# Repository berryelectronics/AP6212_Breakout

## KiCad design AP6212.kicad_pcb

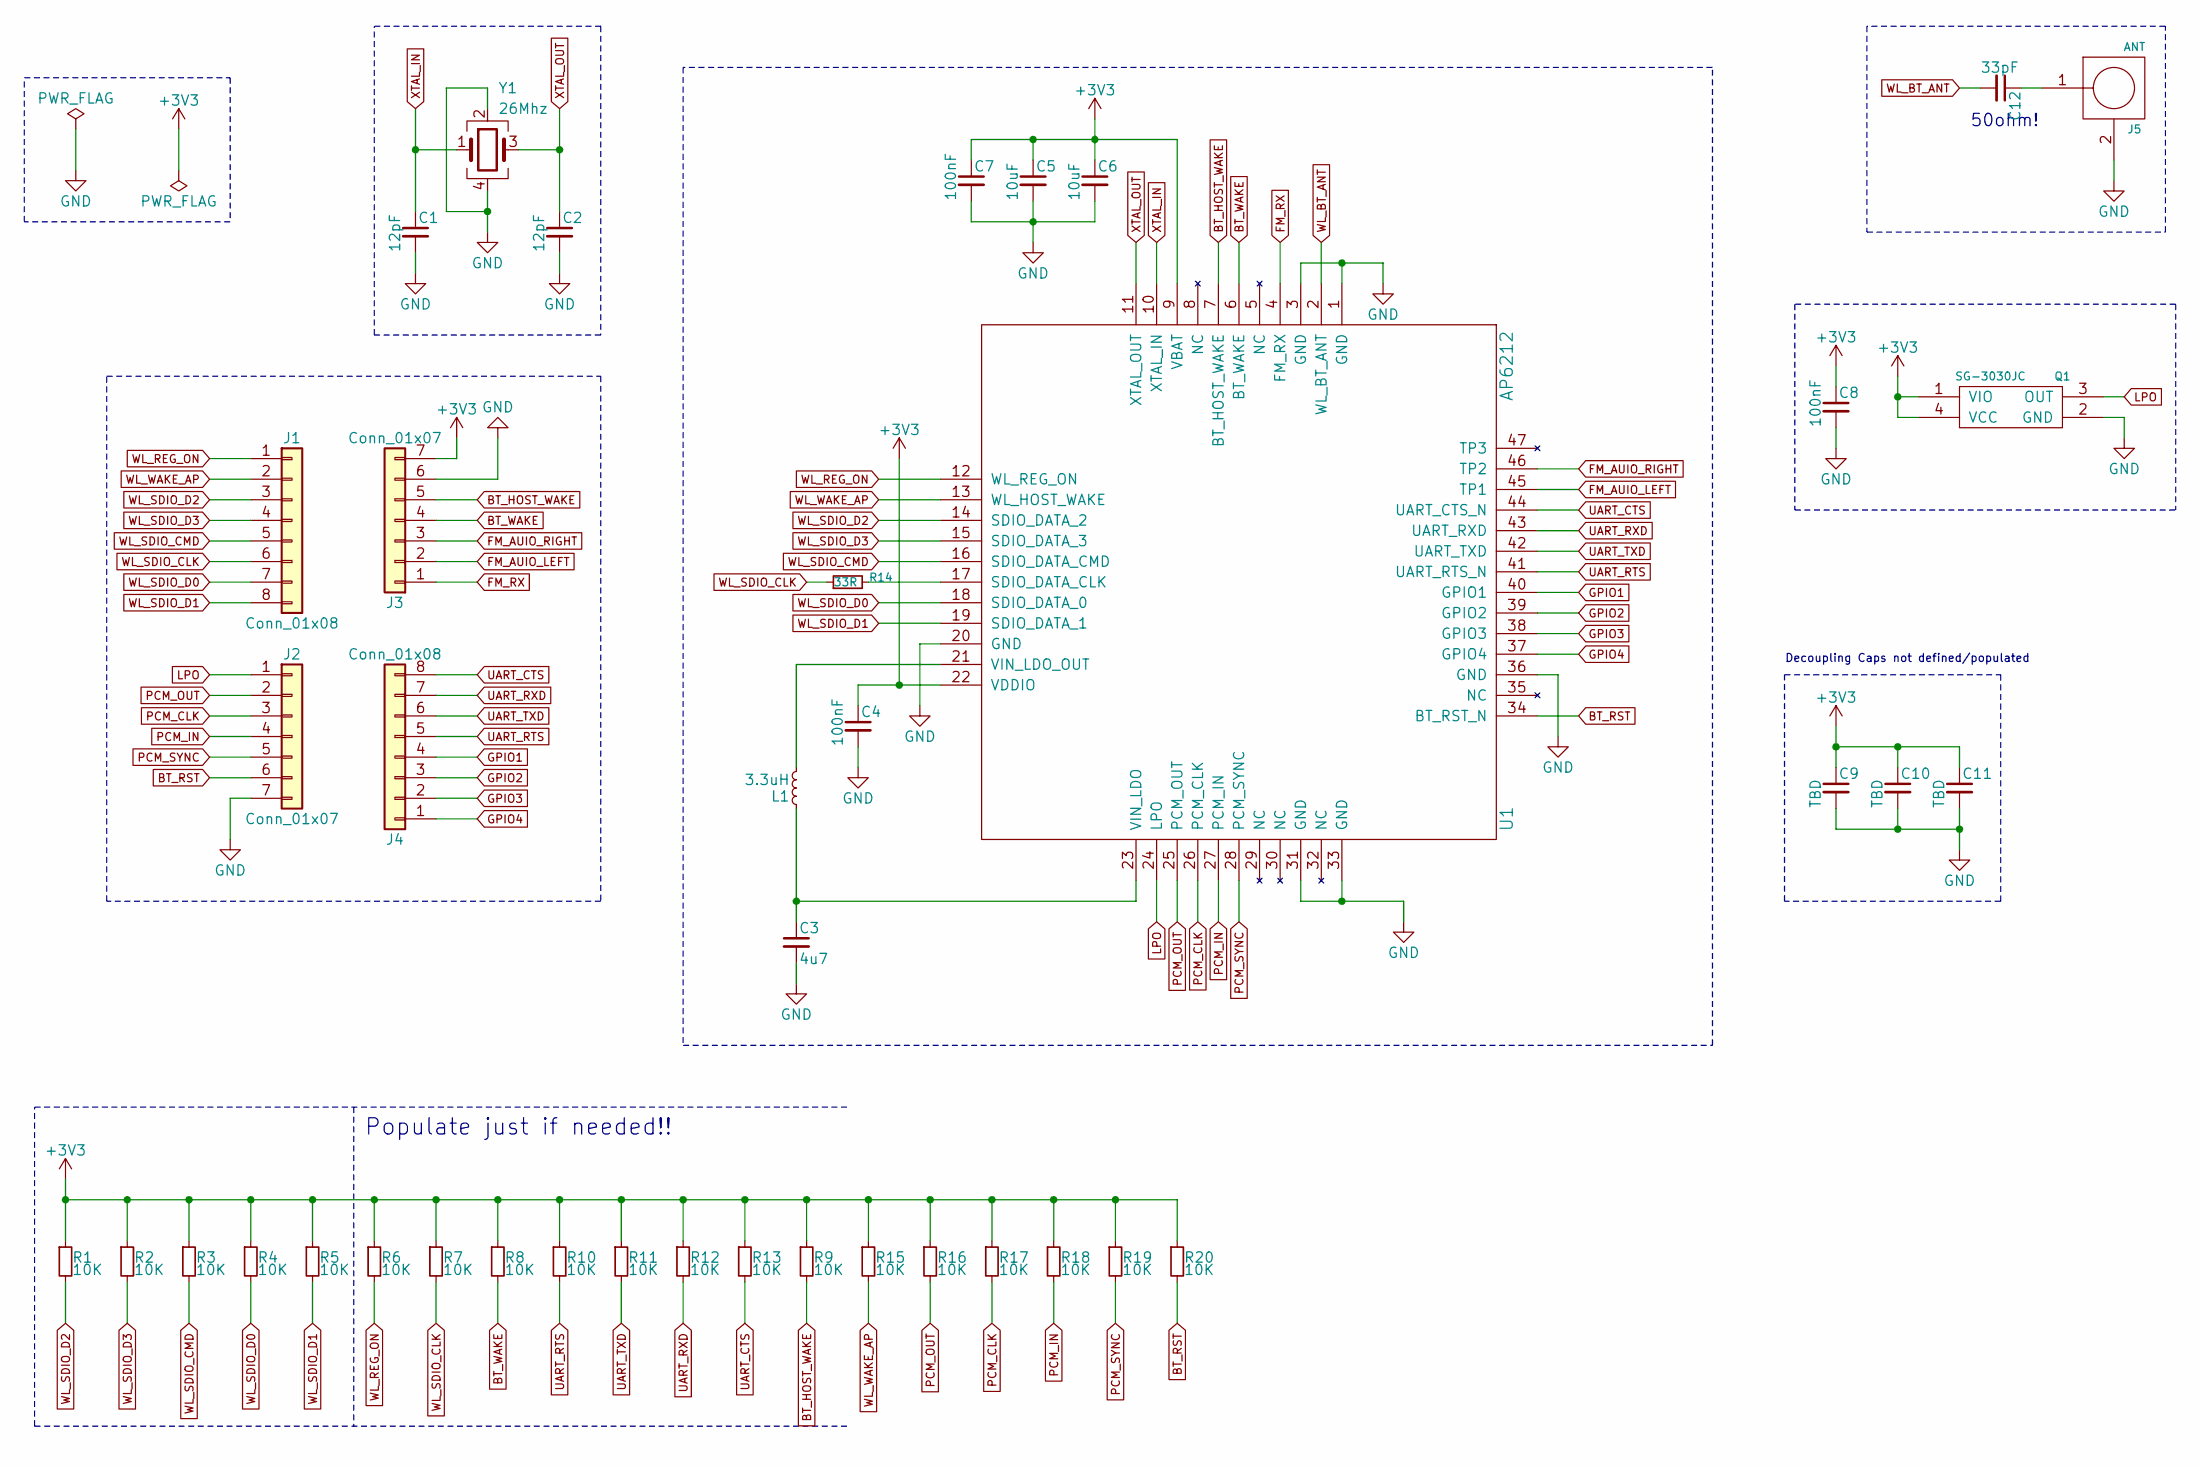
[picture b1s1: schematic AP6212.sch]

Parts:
C1, C2: 12pF; C_0603_HandSoldering
C3: 4u7; C_0603_HandSoldering
C4, C7, C8: 100nF; C_0603_HandSoldering
C5, C6: 10uF; C_0603_HandSoldering
C9, C10, C11: TBD; C_0603_HandSoldering
C12: 33pF; C_0603_HandSoldering
J1, J4: Conn_01x08; Pin_Header_Straight_1x08_Pitch2.54mm
J2, J3: Conn_01x07; Pin_Header_Straight_1x07_Pitch2.54mm
J5: ANT; SMA_THT_Jack_Straight
L1: 3.3uH; R_1206_HandSoldering
Q1: SG-3030JC
R1, R2, R3, R4, R5, R6, R7, R8, R9, R10, R11, R12, R13, R15, R16, R17, R18, R19, R20: 10K; R_0603_HandSoldering
R14: 33R; R_0603_HandSoldering
U1: AP6212
Y1: 26Mhz; 3225-Crystal

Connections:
+3V3: C4.1, C5.1, C6.1, C7.1, C8.1, C9.1, C10.1, C11.1, J3.7, Q1.1 (VIO), Q1.4 (VCC), R1.1, R2.1, R3.1, R4.1, R5.1, R6.1, R7.1, R8.1, R9.1, R10.1, R11.1, R12.1, R13.1, R15.1, R16.1, R17.1, R18.1, R19.1, R20.1, U1.9 (VBAT), U1.22 (VDDIO)
BT_HOST_WAKE: J3.5, R9.2, U1.7 (BT_HOST_WAKE)
BT_RST: J2.6, R20.2, U1.34 (BT_RST_N)
BT_WAKE: J3.4, R8.2, U1.6 (BT_WAKE)
FM_AUIO_LEFT: J3.2, U1.45 (TP1)
FM_AUIO_RIGHT: J3.3, U1.46 (TP2)
FM_RX: J3.1, U1.4 (FM_RX)
GND: C1.2, C2.2, C3.2, C4.2, C5.2, C6.2, C7.2, C8.2, C9.2, C10.2, C11.2, J2.7, J3.6, J5.2, Q1.2 (GND), U1.1 (GND), U1.3 (GND), U1.20 (GND), U1.31 (GND), U1.33 (GND), U1.36 (GND), Y1.2, Y1.4
GPIO1: J4.4, U1.40 (GPIO1)
GPIO2: J4.3, U1.39 (GPIO2)
GPIO3: J4.2, U1.38 (GPIO3)
GPIO4: J4.1, U1.37 (GPIO4)
LPO: J2.1, Q1.3 (OUT), U1.24 (LPO)
unnamed: C3.1, L1.1, U1.23 (VIN_LDO)
unnamed: C12.1, J5.1
unnamed: L1.2, U1.21 (VIN_LDO_OUT)
unnamed: R14.2, U1.17 (SDIO_DATA_CLK)
PCM_CLK: J2.3, R17.2, U1.26 (PCM_CLK)
PCM_IN: J2.4, R18.2, U1.27 (PCM_IN)
PCM_OUT: J2.2, R16.2, U1.25 (PCM_OUT)
PCM_SYNC: J2.5, R19.2, U1.28 (PCM_SYNC)
UART_CTS: J4.8, R13.2, U1.44 (UART_CTS_N)
UART_RTS: J4.5, R10.2, U1.41 (UART_RTS_N)
UART_RXD: J4.7, R12.2, U1.43 (UART_RXD)
UART_TXD: J4.6, R11.2, U1.42 (UART_TXD)
WL_BT_ANT: C12.2, U1.2 (WL_BT_ANT)
WL_REG_ON: J1.1, R6.2, U1.12 (WL_REG_ON)
WL_SDIO_CLK: J1.6, R7.2, R14.1
WL_SDIO_CMD: J1.5, R3.2, U1.16 (SDIO_DATA_CMD)
WL_SDIO_D0: J1.7, R4.2, U1.18 (SDIO_DATA_0)
WL_SDIO_D1: J1.8, R5.2, U1.19 (SDIO_DATA_1)
WL_SDIO_D2: J1.3, R1.2, U1.14 (SDIO_DATA_2)
WL_SDIO_D3: J1.4, R2.2, U1.15 (SDIO_DATA_3)
WL_WAKE_AP: J1.2, R15.2, U1.13 (WL_HOST_WAKE)
XTAL_IN: C1.1, U1.10 (XTAL_IN), Y1.1
XTAL_OUT: C2.1, U1.11 (XTAL_OUT), Y1.3

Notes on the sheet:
Populate just if needed!!
Decoupling Caps not defined/populated
50ohm!

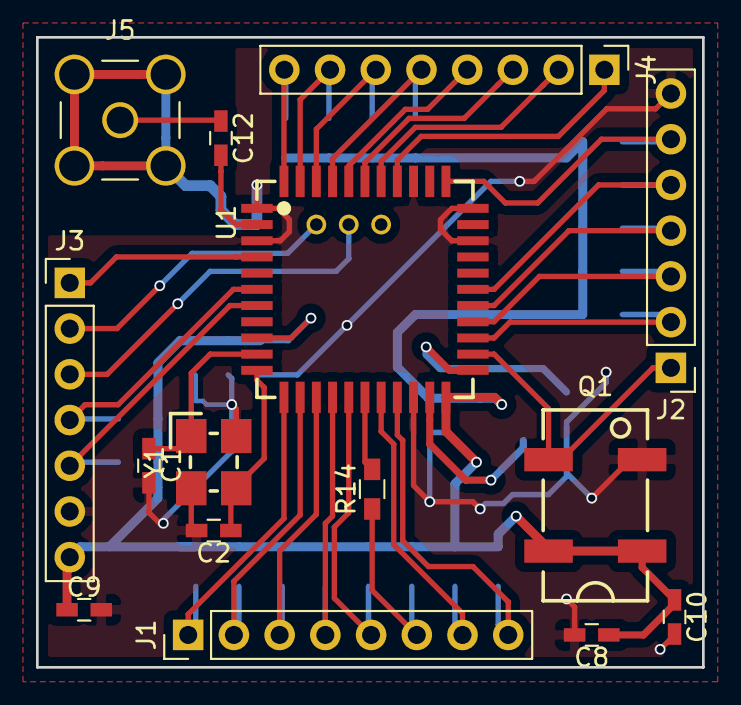
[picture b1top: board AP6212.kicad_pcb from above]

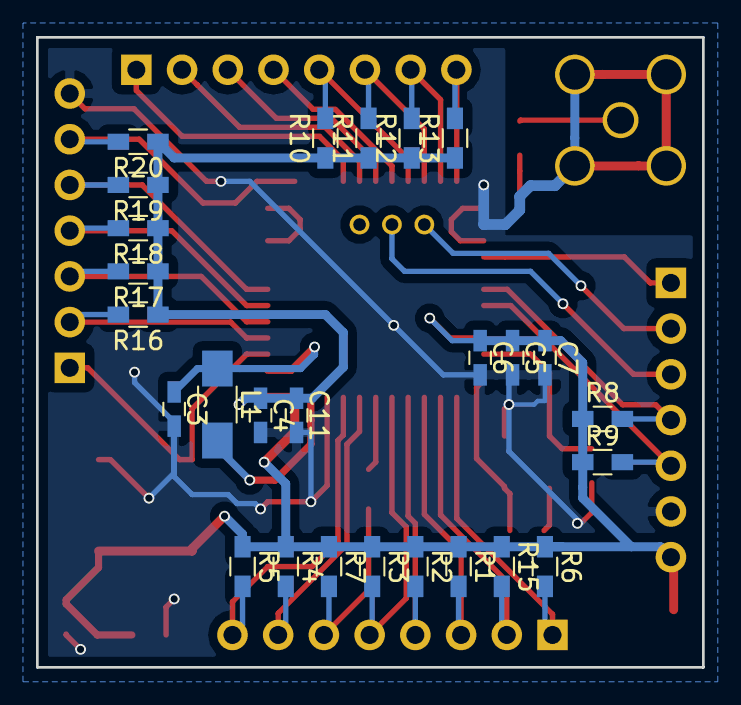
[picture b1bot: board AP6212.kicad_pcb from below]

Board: 2 copper layers, 37.0 x 35.0 mm, 41 parts (26 on the bottom side), 36 nets.

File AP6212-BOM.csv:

"ID";"Bezeichner";"Gehäuse";"Stückzahl";"Bezeichnung";"Anbieter und Ref.";
1;"C1,C2";"C_0603_HandSoldering";2;"12pF";;;
2;"C3";"C_0603_HandSoldering";1;"4u7";;;
3;"C4,C7,C8";"C_0603_HandSoldering";3;"100nF";;;
4;"C5,C6";"C_0603_HandSoldering";2;"10uF";;;
5;"C9,C10,C11";"C_0603_HandSoldering";3;"TBD";;;
6;"J1,J4";"Pin_Header_Straight_1x08_Pitch2.54mm";2;"Conn_01x08";;;
7;"J2,J3";"Pin_Header_Straight_1x07_Pitch2.54mm";2;"Conn_01x07";;;
8;"J5";"SMA_THT_Jack_Straight";1;"ANT";;;
9;"Q1";"SG-3030JC";1;"SG-3030JC";;;
10;"R1,R2,R3,R4,R5,R6,R7,R8,R10,R11,R12,R13,R9,R15,R16,R17,R18,R19,R20";"R_0603_HandSoldering";19;"10K";;;
11;"U1";"AP6212";1;"AP6212";;;
12;"Y1";"3225-Crystal";1;"26Mhz";;;
13;"R14";"R_0603_HandSoldering";1;"33R";;;
14;"L1";"R_1206_HandSoldering";1;"3.3uH";;;
15;"C12";"C_0603_HandSoldering";1;"33pF";;;

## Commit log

2017-11-18 Added all files
2017-11-18 added full bom
